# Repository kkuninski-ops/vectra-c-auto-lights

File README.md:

# Vectra C Auto Lights Controller

Автоматичен контролер за управление на светлините на **Opel Vectra C 2008** с ксенон D1S.
MCU: **ESP32** с вграден Bluetooth (BLE).

## Функции

Всички функции работят **само при AUTO позиция** на копчето за светлини.
При ръчни позиции (0 / габарити / ниски) — factory поведение, контролерът не се намесва.

| Режим | Условие | Светлини |
|-------|---------|---------|
| **Welcome** | Отключване без ключ | конфигурируемо (габарити / мъгла / ксенон) |
| **ACC** | Контакт без двигател | конфигурируемо |
| **DRL** | Двигател работи | ксенон + габарити |
| **Goodbye** | Двигател спира | конфигурируемо |

### DRL — защо така

- Ксенонът светва в момента в който алтернаторът вдига напрежението над 13.2V
- При всяко палене се вижда пълният студен старт на ксенона (синьо/лилаво → бяло) + нивелиране
- Нивелирането е независимо от нашия контролер — задейства се от сигнала на двигателя

### Конфигурация от телефон (BLE)

Свържи се с **"Vectra Auto Lights"** от BLE Terminal приложение и пиши команди:

```
set welcome.lights=GABARI+FOG
set welcome.time=30
set goodbye.lights=GABARI
set goodbye.time=60
set acc.lights=GABARI
set acc.enabled=1
status
reset
```

Вижте [docs/ble-commands.md](docs/ble-commands.md) за пълен списък.

## Хардуер накратко

- **MCU:** ESP32 DevKit v1
- **Ксенон:** IRF4905 P-MOSFET + 2N7000 драйвер (high-side, паралелно на BCM)
- **Габарити / Мъгла:** 12V реле × 2 (паралелно на BCM)
- **Входове:** 3× PC817 оптрон (ACC, AUTO, Unlock) + ADC делител (Vbat)
- **Захранване:** LM7805 от KL30 (постоянно)
- **Защити:** TVS (P6KE15A), реверсна диода, watchdog (ESP32 вграден)

## Структура на репото

```
vectra-c-auto-lights/
├── README.md
├── hardware/
│   └── schematic.md          ← ASCII схема + BOM
├── firmware/
│   ├── platformio.ini        ← PlatformIO конфигурация
│   └── src/
│       ├── main.cpp          ← setup() и loop()
│       ├── common.h          ← споделени константи
│       ├── config.h/cpp      ← конфигурация + NVS съхранение
│       ├── inputs.h/cpp      ← четене на входове + ADC
│       ├── outputs.h/cpp     ← управление на изходи
│       ├── state_machine.h/cpp ← главна логика
│       └── ble_config.h/cpp  ← Bluetooth конфигурация
├── docs/
│   ├── pinout.md             ← точки за свързване в колата
│   └── ble-commands.md       ← BLE команди
└── wiki/                     ← knowledge base
```

## Quick start

1. Инсталирай [PlatformIO](https://platformio.org/)
2. Отвори папка `firmware/` в VS Code
3. Build → Upload към ESP32
4. Свържи се по BLE и провери `status`
5. Свържи хардуера по [hardware/schematic.md](hardware/schematic.md)
6. Намери проводниците в колата по [docs/pinout.md](docs/pinout.md)

## Статус

- [x] Firmware — state machine, BLE, конфигурация
- [x] Хардуерна схема + BOM
- [ ] Намиране на AUTO и Unlock проводници в колата
- [ ] Прототип на breadboard
- [ ] Тест в кола
- [ ] Финален PCB

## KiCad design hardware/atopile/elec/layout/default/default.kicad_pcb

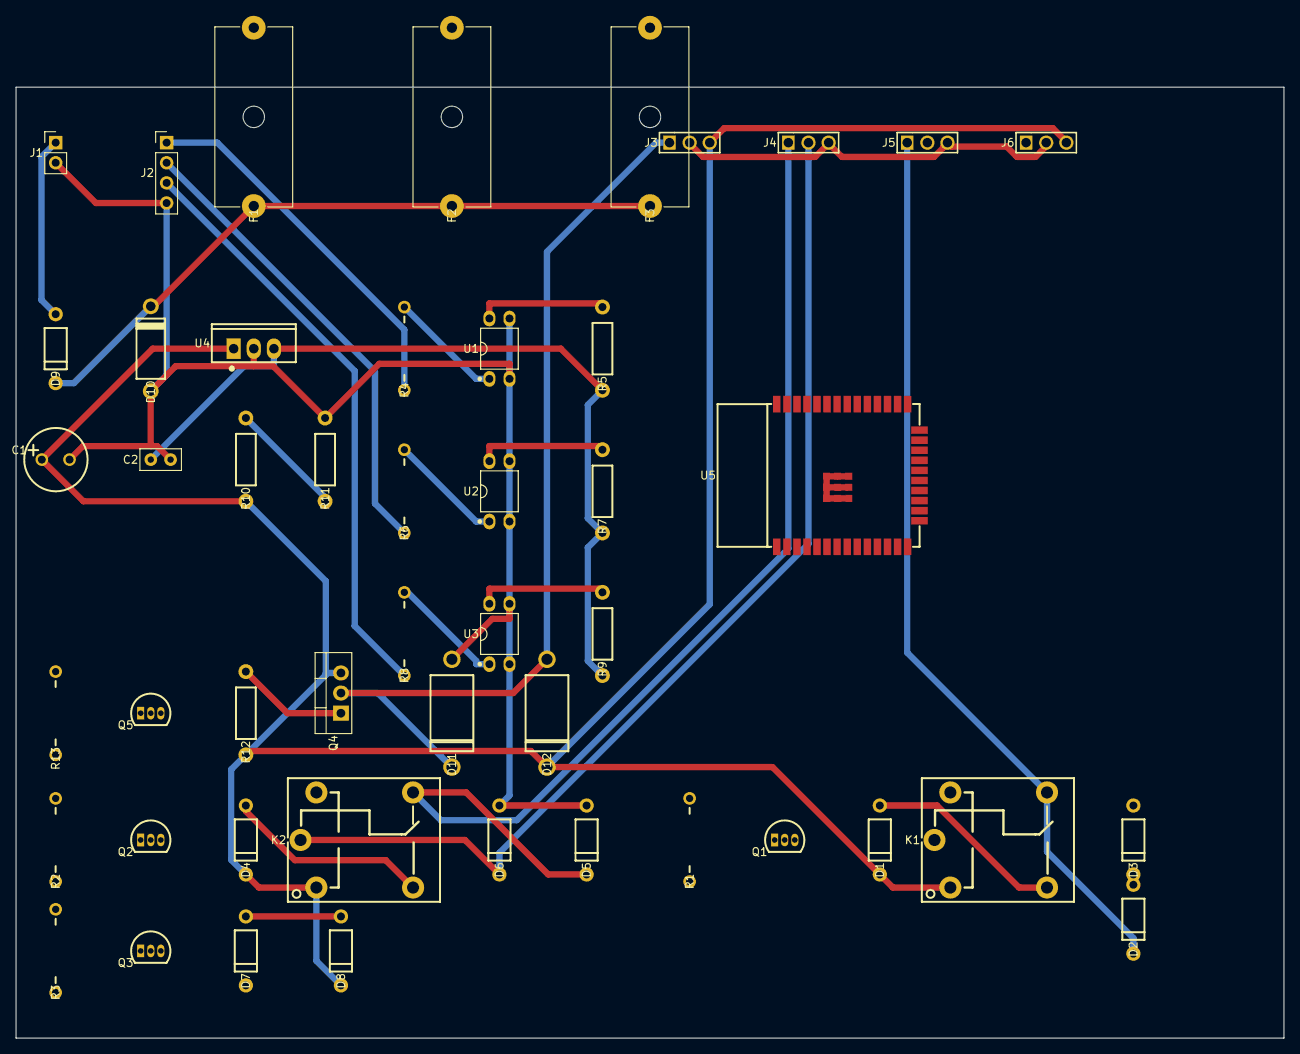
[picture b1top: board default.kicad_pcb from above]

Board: 2 copper layers, 160.0 x 120.0 mm, 48 parts (0 on the bottom side), 32 nets.

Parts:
C1: CAP-TH_BD8.0-P3.50-D0.5-FD
C2: C_Disc_D5.0mm_W2.5mm_P2.50mm
D1, D2, D3, D4, D5, D6, D7, D8, D9: DO-41_BD2.4-L4.7-P8.70-D0.9-RD
D10: DO-15_BD3.1-L6.7-P10.70-D0.9-FD
D11, D12: DO-201_BD5.3-L9.5-P13.50-D1.4-RD
F1, F2, F3: Fuseholder_Cylinder-5x20mm_Schurter_0031_8201_Horizontal_Op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
J1: PinHeader_1x02_P2.54mm_Vertical
J2: PinHeader_1x04_P2.54mm_Vertical
J3, J4, J5, J6: HDR-TH_3P-P2.54-V-M-1
K1, K2: RELAY-TH_SRD-XXVDC-XL-C
Q1, Q2, Q3, Q5: TO-92-3_L4.9-W3.7-P1.27-L
Q4: TO-220-3_Vertical
R1, R2, R3, R4, R6, R8, R13: RES-TH_BD2.2-L6.5-P10.50-D0.6
R5, R7, R9, R10, R11, R12: RES-TH_BD2.5-L6.5-P10.50-D0.6
U1, U2, U3: DIP-4_L4.6-W6.5-P2.54-LS7.6-BL
U4: TO-220-3_L10.0-W4.5-P2.54-L
U5: WIFI-SMD_ESP32-WROOM-32E

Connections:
1: D9.1, D10.2, F1.1, F2.1, F3.1
2: D1.2, K1.2, Q1.1
AN: R4.2, U1.1
D: Q4.1, Q5.3, R12.2
com: D2.1, J5.1, K1.3
com-1: D5.1, J4.1, K2.3
ctrl: R1.1, U5.33
ctrl-1: R2.1, U5.31
ctrl-2: R3.1, U5.36
ctrl-3: R13.1, U5.30
fog-2: Q1.2, R1.2
gabari-2: D4.2, K2.2, Q2.1
gabari-2-1: Q2.2, R2.2
gnd: C1.2, C2.2, D2.2, D3.2, D5.2, D6.2, D7.2, D8.2, D10.1, D11.2, J1.2, J2.4, J3.2, J4.3, J5.3, J6.2, Q1.3, Q2.3, Q3.3, Q5.1, R11.2, U1.2, U1.3, U2.2, U2.3, U3.2, U3.3, U4.2, U5.1, U5.15, U5.38, U5.39
illum-2: Q3.2, R3.2
no: D3.1, J5.2, K1.5
no-1: D6.1, J4.2, K2.5
ok2-AN: R6.2, U2.1
ok3-AN: R8.2, U3.1
out_illum: D7.1, J6.1, Q3.1
out_xenon: D11.1, D12.2, J3.1, Q4.2
sig_auto: J2.2, R6.1
sig_in: J2.1, R4.1
sig_out: R5.2, U1.4, U5.27
sig_out-1: R7.2, U2.4, U5.28
sig_out-2: R9.2, U3.4, U5.29
sig_unlock: J2.3, R8.1
v12: C1.1, D1.1, D4.1, D8.1, D12.1, F1.2, F2.2, F3.2, J3.3, J6.3, K1.1, K2.1, Q4.3, R10.1, R12.1, U4.1
v33: C2.1, R5.1, R7.1, R9.1, U4.3, U5.2
vin_raw: D9.2, J1.1
vout: R10.2, R11.1, U5.26
xenon-2: Q5.2, R13.2

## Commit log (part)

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2026-05-06 Initial commit — Vectra C Auto Lights Controller (ESP32 + BLE)
2026-05-06 Add illumination output — radio/cluster brightness follows AUTO state
